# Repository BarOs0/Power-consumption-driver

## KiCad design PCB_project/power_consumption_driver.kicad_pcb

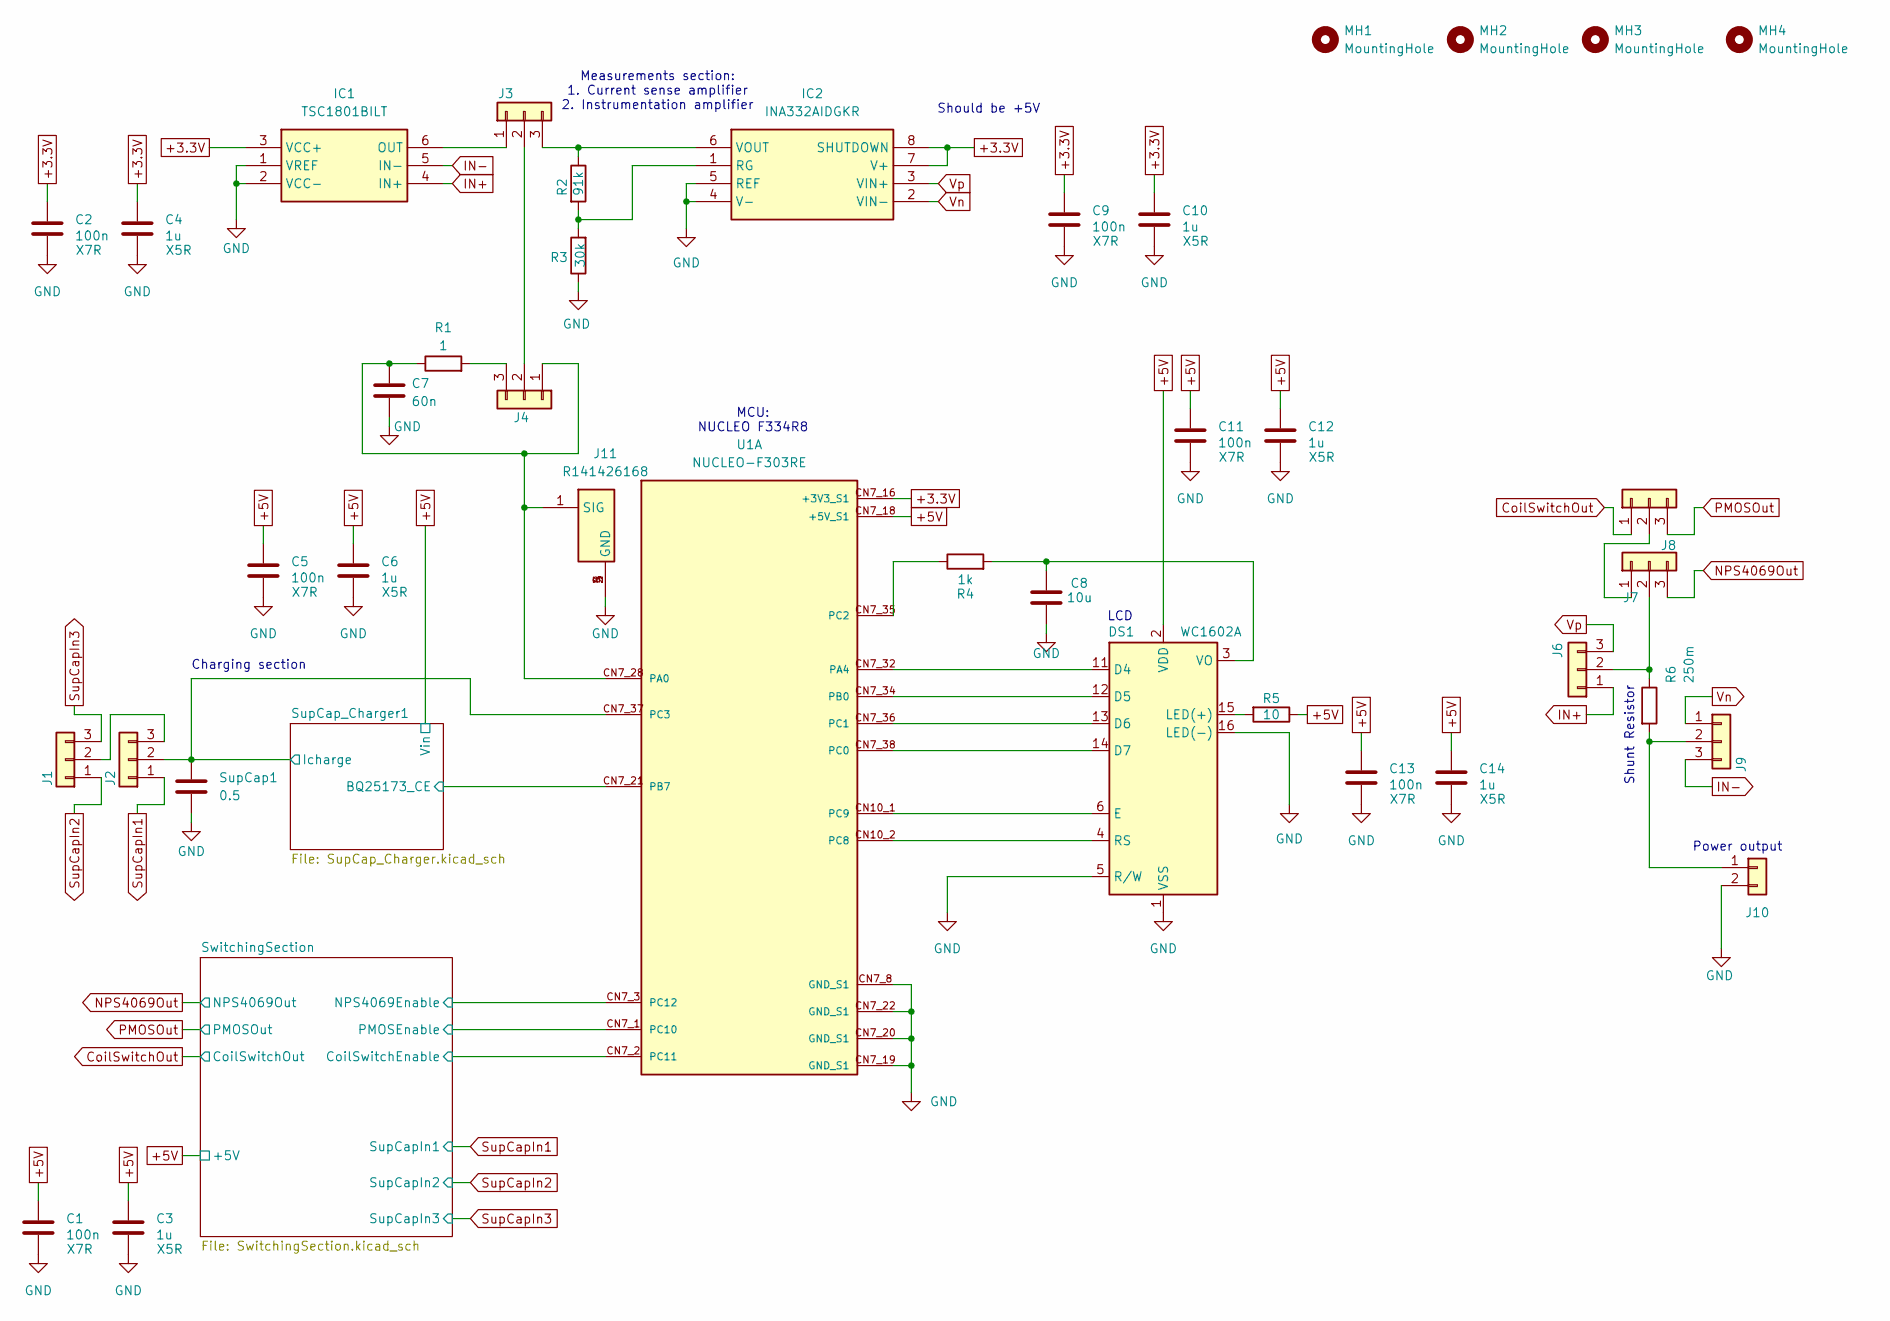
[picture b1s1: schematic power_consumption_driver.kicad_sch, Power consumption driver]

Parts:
C1, C2, C5, C9, C11, C13: 100n; C_0402_1005Metric_Pad0.74x0.62mm_HandSolder
C3, C4, C6, C10, C12, C14: 1u; C_0402_1005Metric_Pad0.74x0.62mm_HandSolder
C7: 60n; C_0402_1005Metric_Pad0.74x0.62mm_HandSolder
C8: 10u; C_0402_1005Metric_Pad0.74x0.62mm_HandSolder
DS1: WC1602A
IC1: TSC1801BILT; SOT95P280X145-6N; Manufacturer_Part_Number TSC1801BILT
IC2: INA332AIDGKR; SOP65P490X110-8N; Manufacturer_Part_Number INA332AIDGKR; Mouser Part Number 595-INA332AIDGKR
J1, J2, J3, J4, J6, J7, J8, J9: Conn_01x03; PinHeader_1x03_P2.54mm_Vertical
J10: Conn_01x02; PinHeader_1x02_P2.54mm_Vertical
J11: R141426168; Manufacturer_Part_Number R141426168; Mouser Part Number 501-R141426168
MH1, MH2, MH3, MH4: MountingHole; MountingHole_3.2mm_M3_ISO14580_Pad
R1: 1; R_0805_2012Metric_Pad1.20x1.40mm_HandSolder
R2: 91k; R_0805_2012Metric_Pad1.20x1.40mm_HandSolder
R3: 30k; R_0805_2012Metric_Pad1.20x1.40mm_HandSolder
R4: 1k; R_0805_2012Metric_Pad1.20x1.40mm_HandSolder
R5: 10; R_0805_2012Metric_Pad1.20x1.40mm_HandSolder
R6: 250m; R_0805_2012Metric_Pad1.20x1.40mm_HandSolder
SupCap1: 0.5; C_Radial_D8.0mm_H11.5mm_P3.50mm
U1: NUCLEO-F303RE; ST_NUCLEO-F303RE; PARTREV 14

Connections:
+3.3V: C2.1, C4.1, C9.1, C10.1, IC1.3 (VCC+), IC2.7 (V+), IC2.8 (SHUTDOWN), U1.CN7_16 (+3V3_S1)
+5V: C1.1, C3.1, C5.1, C6.1, C11.1, C12.1, C13.1, C14.1, DS1.2 (VDD), R5.1, U1.CN7_18 (+5V_S1); also elsewhere on the board
/SupCap_Charger1/BQ25173_CE: U1.CN7_21 (PB7); also elsewhere on the board
/SupCap_Charger1/Icharge: J2.2, SupCap1.1, U1.CN7_37 (PC3); also elsewhere on the board
/SwitchingSection/CoilSwitchEnable: U1.CN7_2 (PC11); also elsewhere on the board
/SwitchingSection/NPS4069Enable: U1.CN7_3 (PC12); also elsewhere on the board
/SwitchingSection/PMOSEnable: U1.CN7_1 (PC10); also elsewhere on the board
CoilSwitchOut: J7.1; also elsewhere on the board
GND: C1.2, C2.2, C3.2, C4.2, C5.2, C6.2, C7.2, C8.2, C9.2, C10.2, C11.2, C12.2, C13.2, C14.2, DS1.1 (VSS), DS1.5 (R/W), DS1.16 (LED(-)), IC1.1 (VREF), IC1.2 (VCC-), IC2.4 (V-), IC2.5 (REF), J10.2, J11.2 (GND), J11.3 (GND), J11.4 (GND), J11.5 (GND), R3.1, SupCap1.2, U1.CN7_8 (GND_S1), U1.CN7_19 (GND_S1), U1.CN7_20 (GND_S1), U1.CN7_22 (GND_S1); also elsewhere on the board
IN+: IC1.4 (IN+), J6.1
IN-: IC1.5 (IN-), J9.3
NPS4069Out: J8.3; also elsewhere on the board
unnamed: DS1.11 (D4), U1.CN7_32 (PA4)
unnamed: DS1.12 (D5), U1.CN7_34 (PB0)
unnamed: DS1.13 (D6), U1.CN7_36 (PC1)
unnamed: DS1.14 (D7), U1.CN7_38 (PC0)
unnamed: DS1.6 (E), U1.CN10_1 (PC9)
unnamed: DS1.15 (LED(+)), R5.2
unnamed: DS1.4 (RS), U1.CN10_2 (PC8)
unnamed: C8.1, DS1.3 (VO), R4.2
unnamed: IC1.6 (OUT), J3.1
unnamed: IC2.1 (RG), R2.2, R3.2
unnamed: IC2.6 (VOUT), J3.3, R2.1
unnamed: J1.2, J2.3
unnamed: J3.2, J4.2
unnamed: J4.3, R1.2
unnamed: J6.2, J8.2, R6.1
unnamed: J7.2, J8.1
unnamed: J9.2, J10.1, R6.2
unnamed: C7.1, J4.1, J11.1 (SIG), R1.1, U1.CN7_28 (PA0)
unnamed: R4.1, U1.CN7_35 (PC2)
PMOSOut: J7.3; also elsewhere on the board
SupCapIn1: J2.1; also elsewhere on the board
SupCapIn2: J1.1; also elsewhere on the board
SupCapIn3: J1.3; also elsewhere on the board
Vn: IC2.2 (VIN-), J9.1
Vp: IC2.3 (VIN+), J6.3

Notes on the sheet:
Should be +5V
Shunt Resistor
Measurements section: 1. Current sense amplifier 2. Instrumentation amplifier
MCU: NUCLEO F334R8
Charging section
Power output
LCD

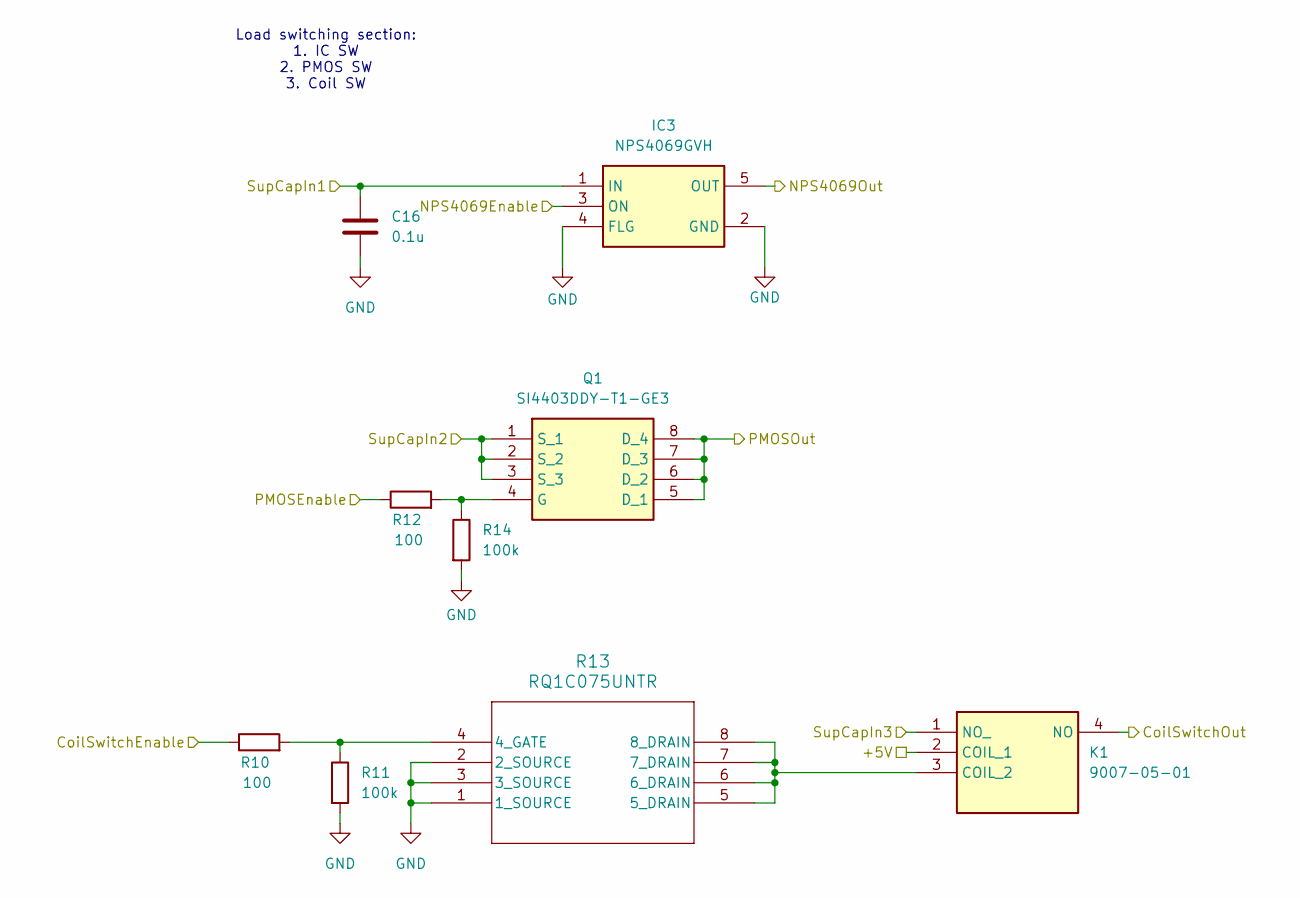
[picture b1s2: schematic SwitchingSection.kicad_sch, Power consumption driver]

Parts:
C16: 0.1u; C_0402_1005Metric_Pad0.74x0.62mm_HandSolder
IC3: NPS4069GVH; SOT95P275X110-5N; Manufacturer_Part_Number NPS4069GVH
K1: 9007-05-01; 90070501; Manufacturer_Part_Number 9007-05-01; Mouser Part Number 816-9007-05-01
Q1: SI4403DDY-T1-GE3; SOIC127P600X175-8N; Manufacturer_Part_Number SI4403DDY-T1-GE3; Mouser Part Number 78-SI4403DDY-T1-GE3
R10, R12: 100; R_0805_2012Metric_Pad1.20x1.40mm_HandSolder
R11, R14: 100k; R_0805_2012Metric_Pad1.20x1.40mm_HandSolder
R13: RQ1C075UNTR; TRANS_RQ1A070Z_ROM

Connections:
+5V: K1.2 (COIL_1); also elsewhere on the board
/SwitchingSection/CoilSwitchEnable: R10.1; also elsewhere on the board
/SwitchingSection/NPS4069Enable: IC3.3 (ON); also elsewhere on the board
/SwitchingSection/PMOSEnable: R12.1; also elsewhere on the board
CoilSwitchOut: K1.4 (NO); also elsewhere on the board
GND: C16.2, IC3.2 (GND), IC3.4 (FLG), R11.2, R13.1 (1_SOURCE), R13.2 (2_SOURCE), R13.3 (3_SOURCE), R14.2; also elsewhere on the board
NPS4069Out: IC3.5 (OUT); also elsewhere on the board
unnamed: K1.3 (COIL_2), R13.5 (5_DRAIN), R13.6 (6_DRAIN), R13.7 (7_DRAIN), R13.8 (8_DRAIN)
unnamed: Q1.4 (G), R12.2, R14.1
unnamed: R10.2, R11.1, R13.4 (4_GATE)
PMOSOut: Q1.5 (D_1), Q1.6 (D_2), Q1.7 (D_3), Q1.8 (D_4); also elsewhere on the board
SupCapIn1: C16.1, IC3.1 (IN); also elsewhere on the board
SupCapIn2: Q1.1 (S_1), Q1.2 (S_2), Q1.3 (S_3); also elsewhere on the board
SupCapIn3: K1.1 (NO_); also elsewhere on the board

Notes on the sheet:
Load switching section: 1. IC SW 2. PMOS SW 3. Coil SW

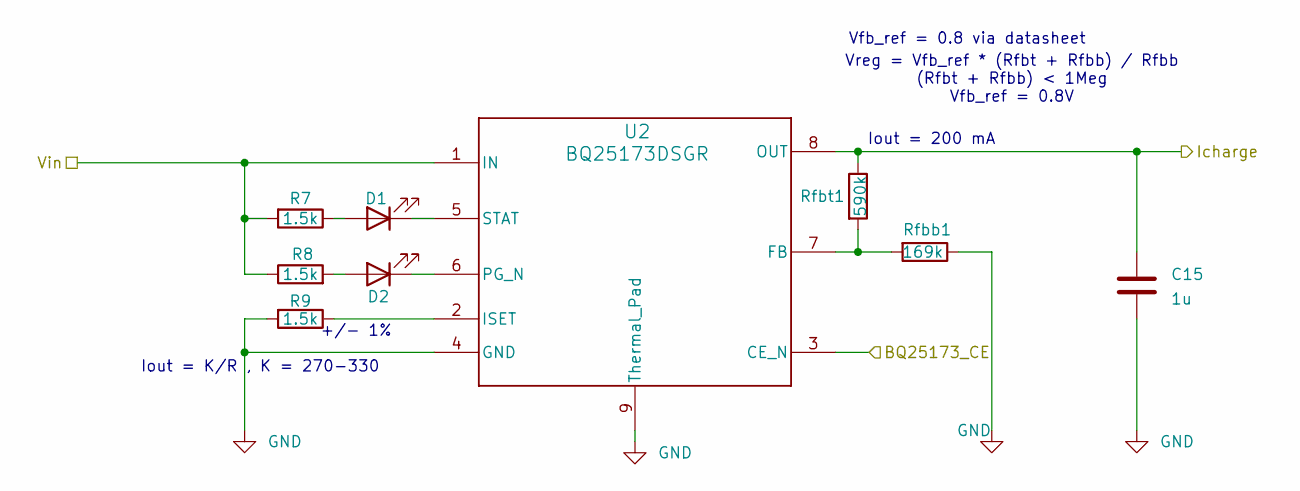
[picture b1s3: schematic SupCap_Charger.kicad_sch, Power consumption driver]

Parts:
C15: 1u; C_0402_1005Metric_Pad0.74x0.62mm_HandSolder
D1, D2: LED; LED_D3.0mm_Clear
R7, R8, R9: 1.5k; R_0805_2012Metric_Pad1.20x1.40mm_HandSolder
Rfbb1: 169k; R_0805_2012Metric_Pad1.20x1.40mm_HandSolder
Rfbt1: 590k; R_0805_2012Metric_Pad1.20x1.40mm_HandSolder
U2: BQ25173DSGR; SON50P200X200X80-9N

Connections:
+5V: R7.2, R8.1, U2.1 (IN); also elsewhere on the board
/SupCap_Charger1/BQ25173_CE: U2.3 (CE_N); also elsewhere on the board
/SupCap_Charger1/Icharge: C15.2, Rfbt1.1, U2.8 (OUT); also elsewhere on the board
GND: C15.1, R9.2, Rfbb1.1, U2.4 (GND), U2.9 (Thermal_Pad); also elsewhere on the board
unnamed: D1.2 (A), R7.1
unnamed: D1.1 (K), U2.5 (STAT)
unnamed: D2.2 (A), R8.2
unnamed: D2.1 (K), U2.6 (PG_N)
unnamed: Rfbb1.2, Rfbt1.2, U2.7 (FB)
unnamed: R9.1, U2.2 (ISET)

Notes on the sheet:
Iout = 200 mA
Vfb_ref = 0.8 via datasheet
Iout = K/R , K = 270-330
Vreg = Vfb_ref * (Rfbt + Rfbb) / Rfbb (Rfbt + Rfbb) < 1Meg Vfb_ref = 0.8V
+/- 1%

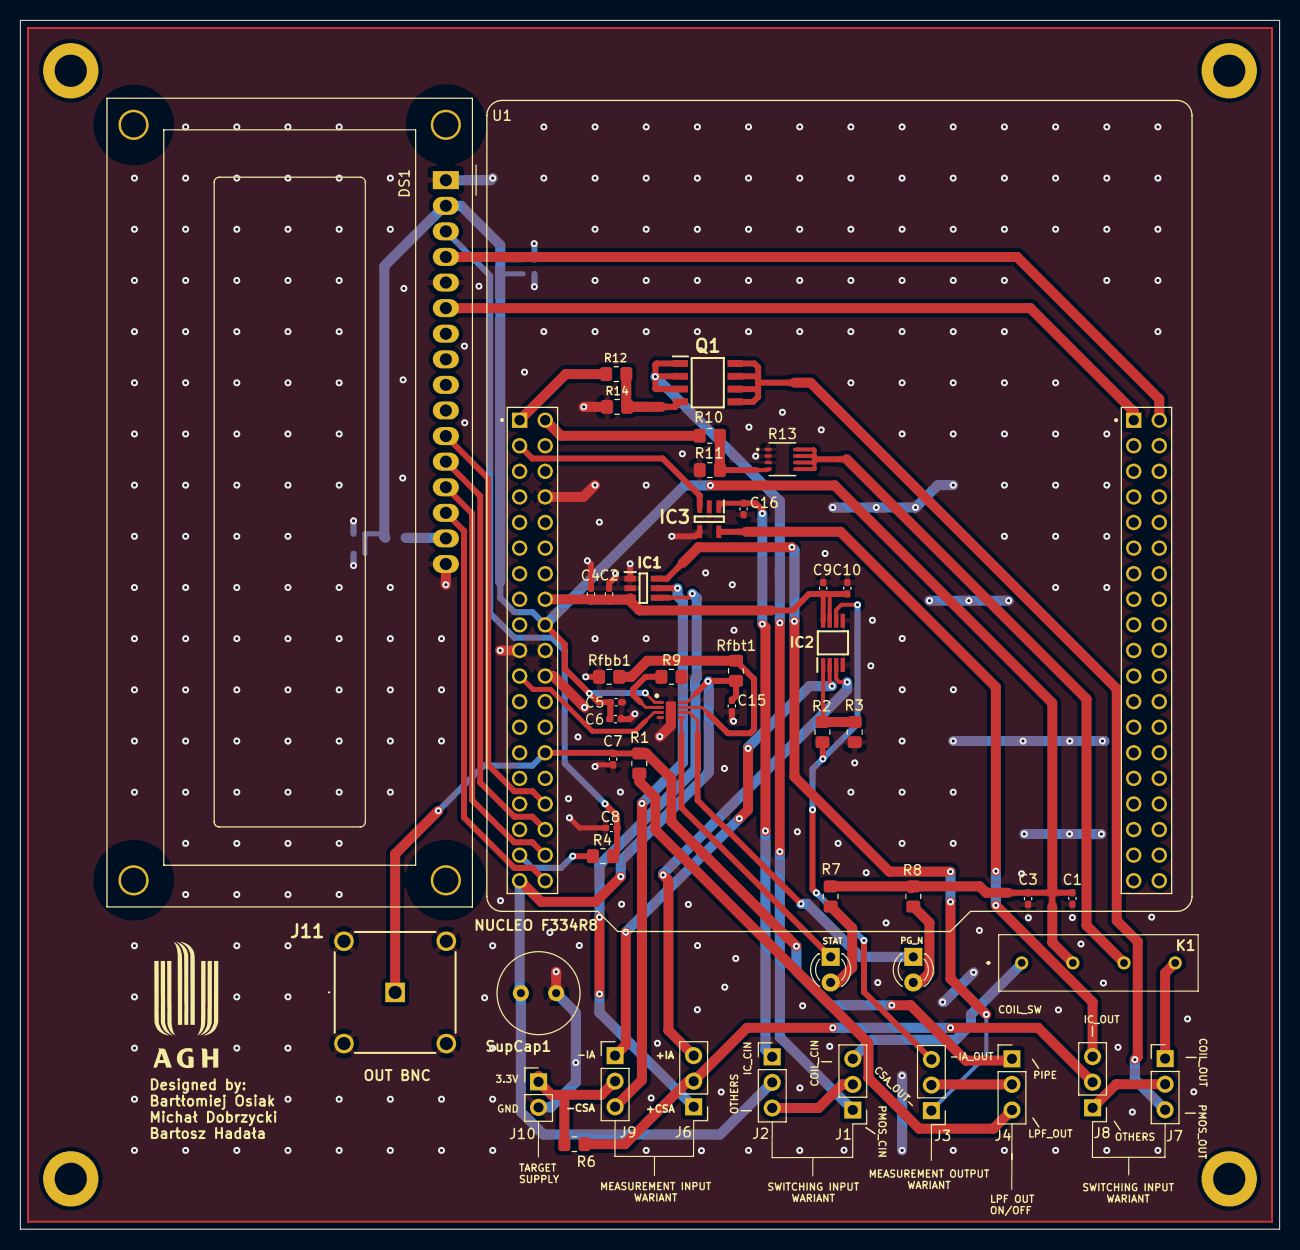
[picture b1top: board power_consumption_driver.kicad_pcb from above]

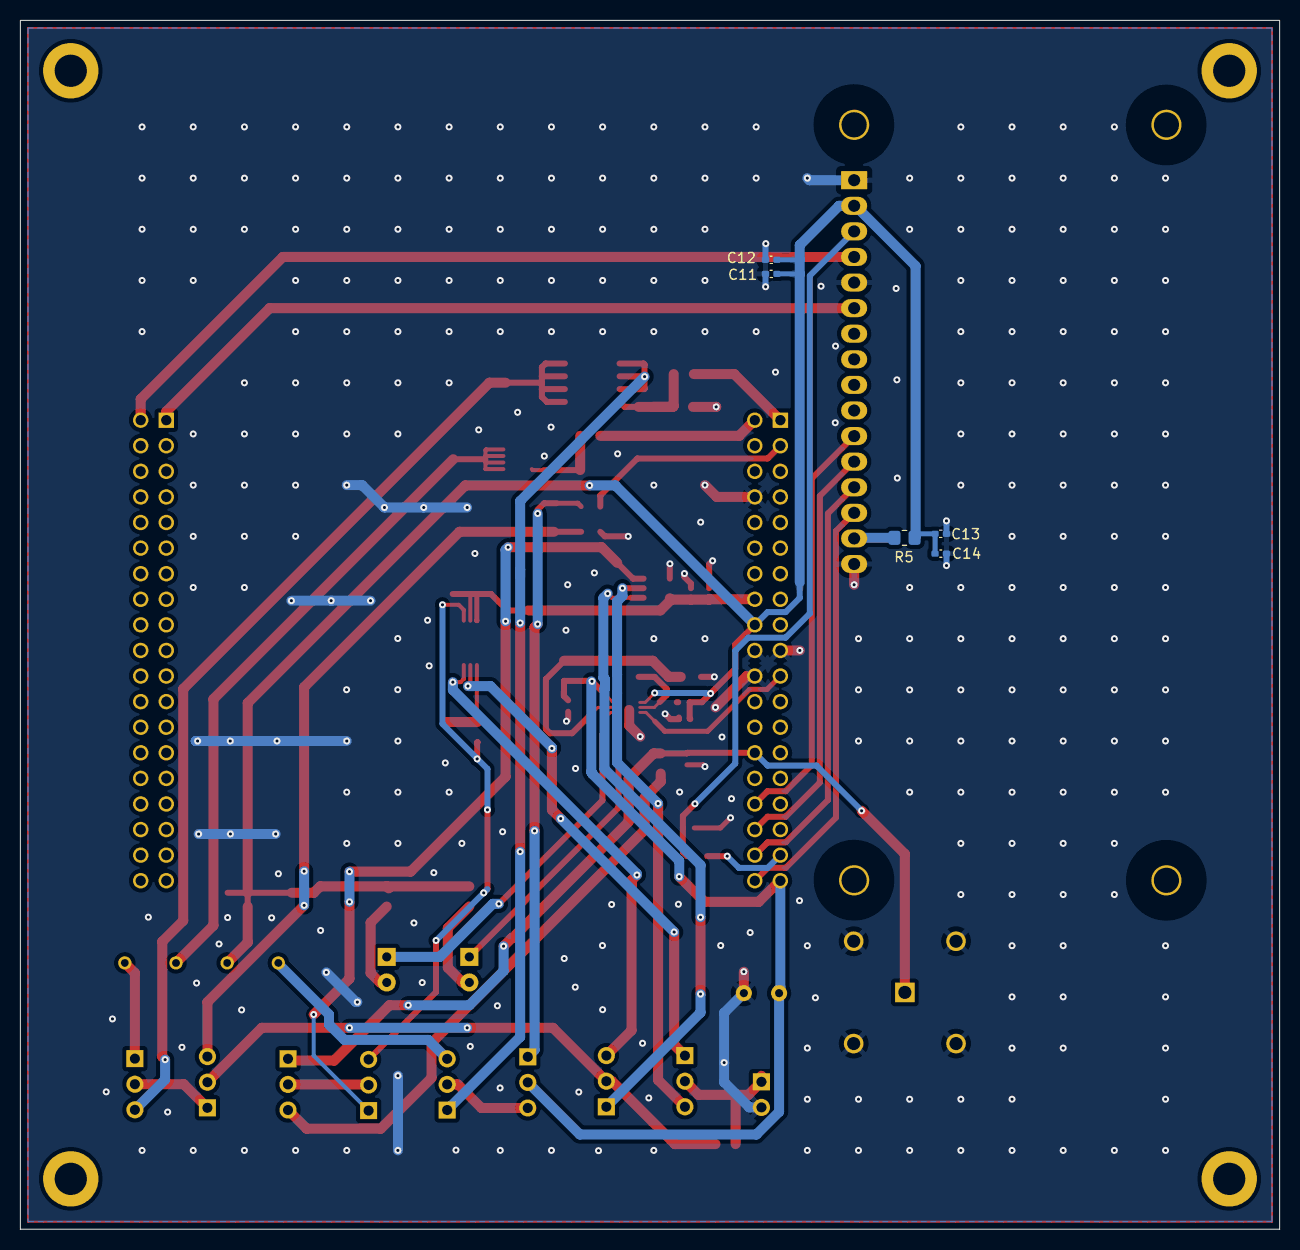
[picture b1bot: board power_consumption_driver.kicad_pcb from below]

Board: 2 copper layers, 125.0 x 120.0 mm, 57 parts (5 on the bottom side), 46 nets.

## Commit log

2026-01-12 KiCad project
2026-01-13 new items
2026-01-20 docs&info
2026-02-10 new files
